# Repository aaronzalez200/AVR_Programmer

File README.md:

# AVR_Programmer

Small board with mounting holes that was designed to easily place an Arduino that runs software that programs an external board that contains an AVR chip via ICSP. Display included to show the user the testing process and if any errors have occurred.

Designed using KiCad

Early prototype using Arduino MEGA later updated for UNO:

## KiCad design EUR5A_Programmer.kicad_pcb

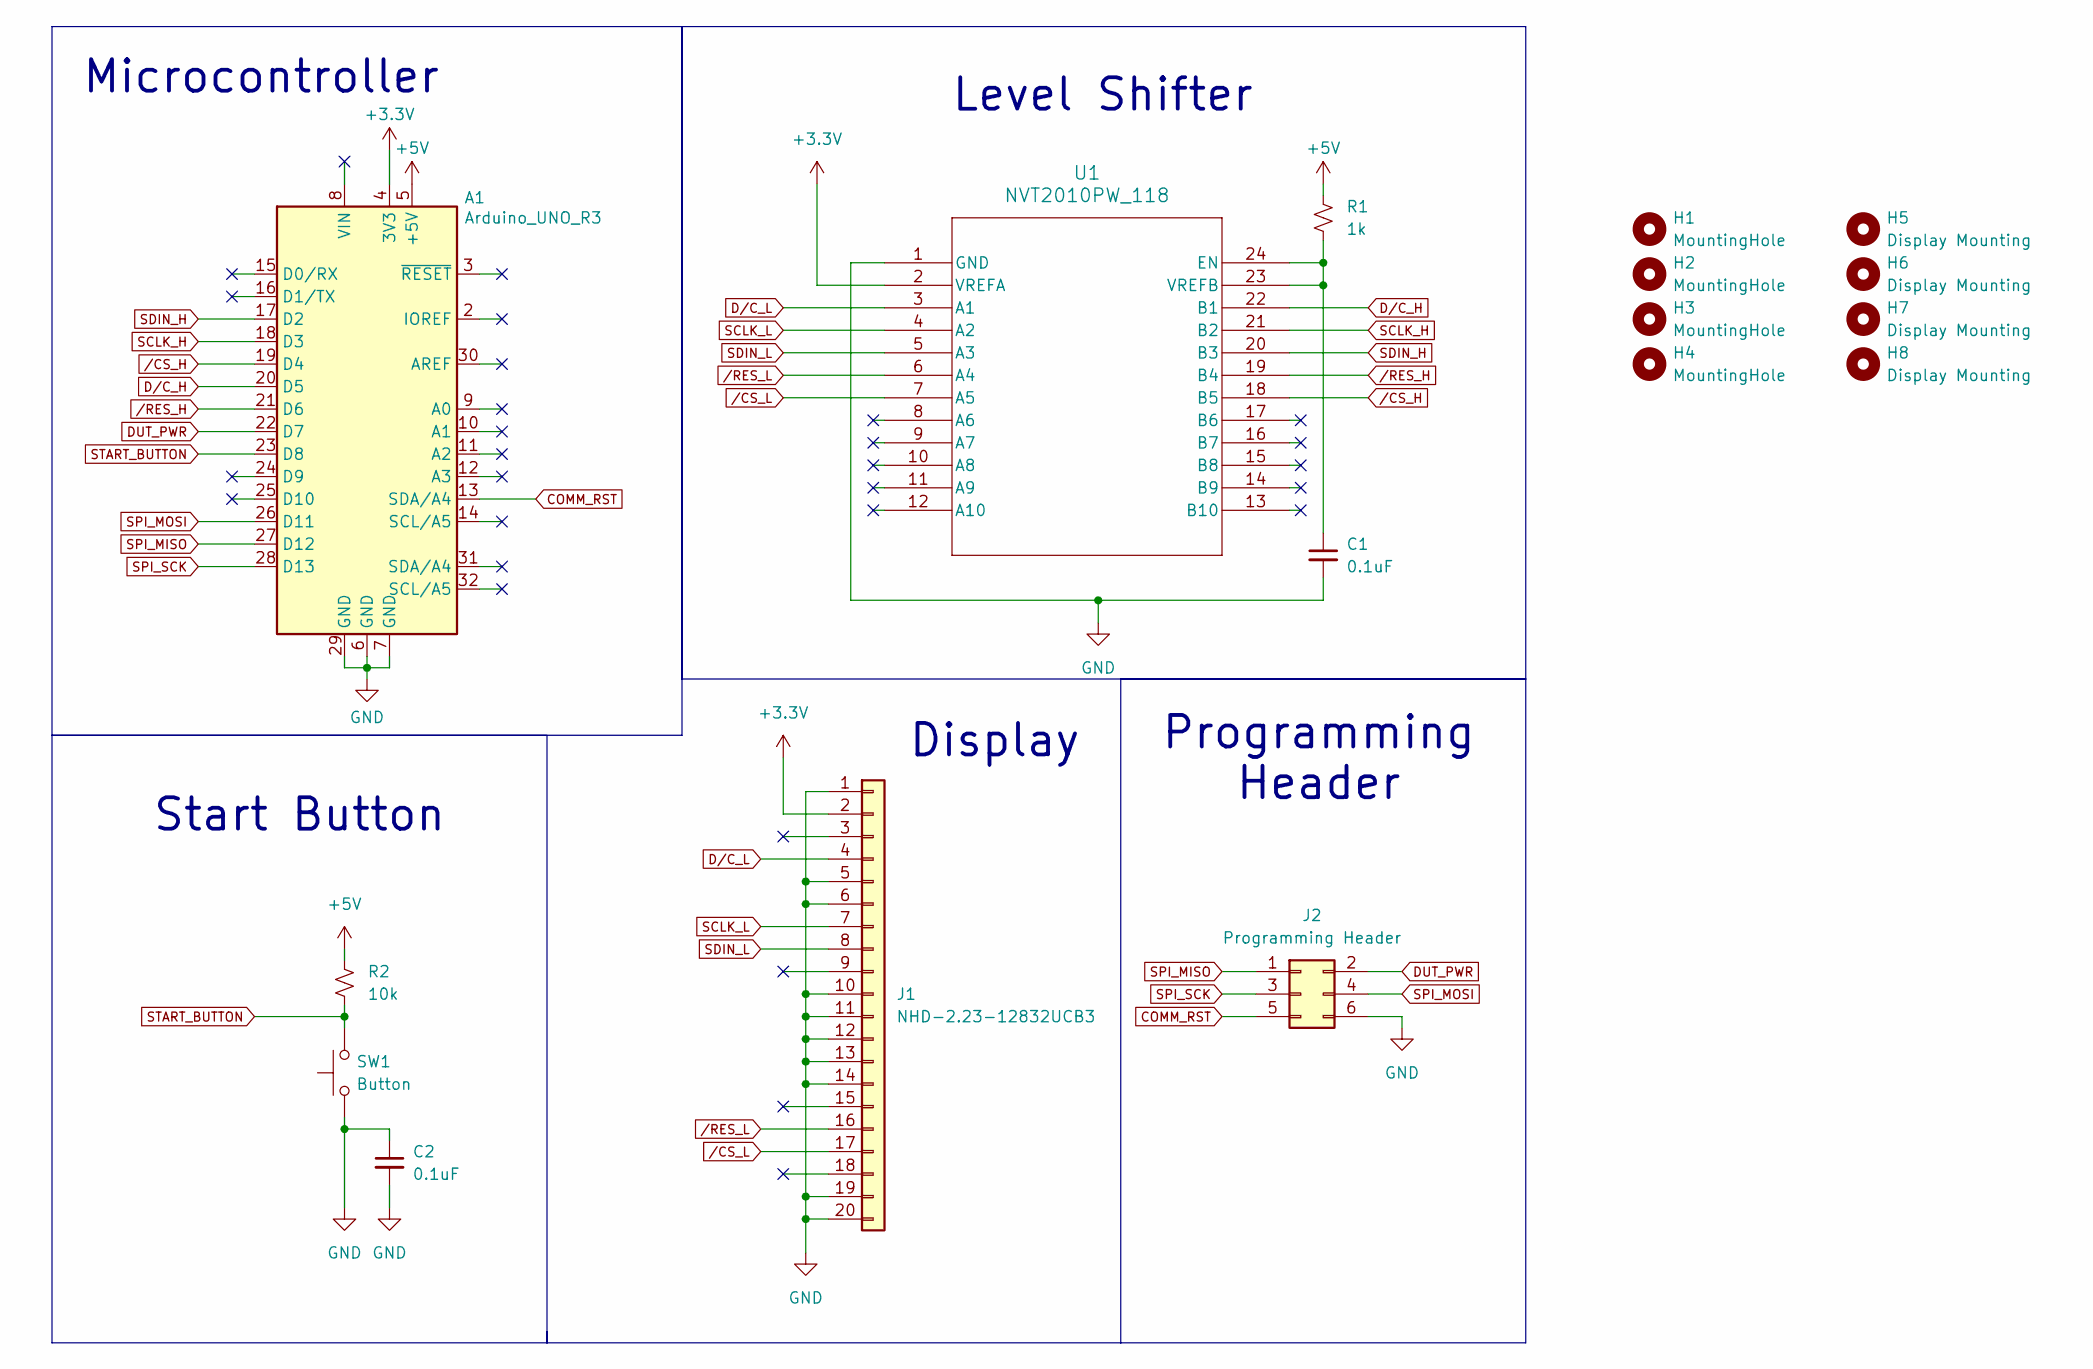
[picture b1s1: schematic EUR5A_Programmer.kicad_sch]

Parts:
A1: Arduino_UNO_R3
C1, C2: 0.1uF; C_Axial_L3.8mm_D2.6mm_P7.50mm_Horizontal
H1, H2, H3, H4: MountingHole; MountingHole_3mm
H5, H6, H7, H8: Display Mounting; Display_Mounting_Hole
J1: NHD-2.23-12832UCB3; PinHeader_1x20_P2.54mm_Vertical
J2: Programming Header; IDC-Header_2x03_P2.54mm_Vertical
R1: 1k; R_Axial_DIN0411_L9.9mm_D3.6mm_P12.70mm_Horizontal
R2: 10k; R_Axial_DIN0411_L9.9mm_D3.6mm_P12.70mm_Horizontal
SW1: Button; TerminalBlock_bornier-2_P5.08mm
U1: NVT2010PW_118; TSSOP24_SOT355-1_NXP

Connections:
+3.3V: A1.4 (3V3), J1.2, U1.2 (VREFA)
+5V: A1.5 (+5V), R1.1, R2.1
COMM_RST: A1.13 (SDA/A4), J2.5
DUT_PWR: A1.22 (D7), J2.2
D/C_H: A1.20 (D5), U1.22 (B1)
D/C_L: J1.4, U1.3 (A1)
GND: A1.6 (GND), A1.7 (GND), A1.29 (GND), C1.2, C2.1, C2.2, J1.1, J1.5, J1.6, J1.10, J1.11, J1.12, J1.13, J1.14, J1.19, J1.20, J2.6, SW1.1, U1.1 (GND)
unnamed: C1.1, R1.2, U1.23 (VREFB), U1.24 (EN)
SCLK_H: A1.18 (D3), U1.21 (B2)
SCLK_L: J1.7, U1.4 (A2)
SDIN_H: A1.17 (D2), U1.20 (B3)
SDIN_L: J1.8, U1.5 (A3)
SPI_MISO: A1.27 (D12), J2.1
SPI_MOSI: A1.26 (D11), J2.4
SPI_SCK: A1.28 (D13), J2.3
START_BUTTON: A1.23 (D8), R2.2, SW1.2
/CS_H: A1.19 (D4), U1.18 (B5)
/CS_L: J1.17, U1.7 (A5)
/RES_H: A1.21 (D6), U1.19 (B4)
/RES_L: J1.16, U1.6 (A4)

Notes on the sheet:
Start Button
Microcontroller
Programming Header
Display
Level Shifter

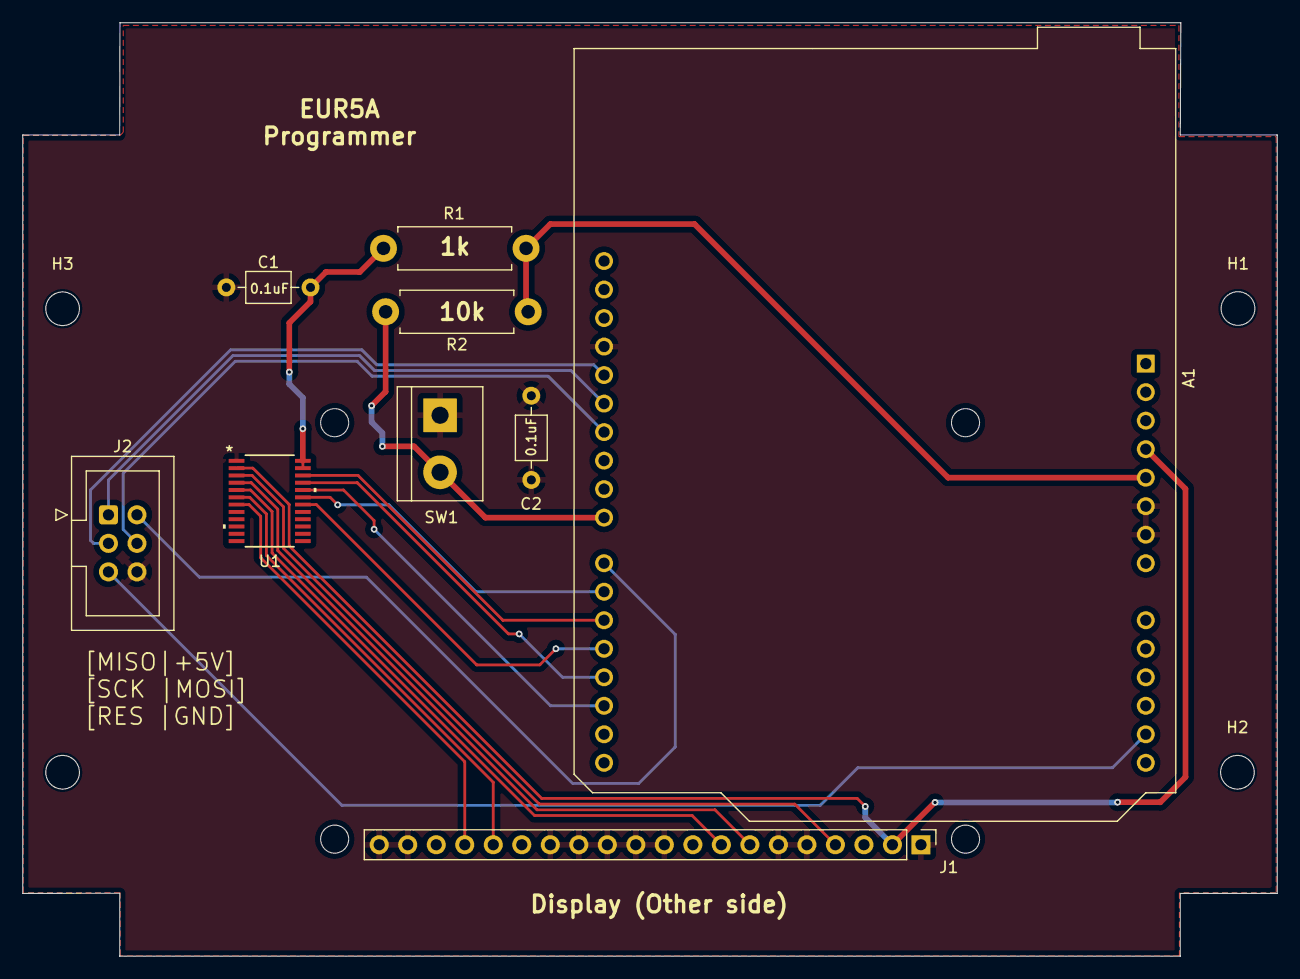
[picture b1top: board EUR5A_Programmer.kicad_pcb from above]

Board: 2 copper layers, 111.8 x 83.2 mm, 17 parts (0 on the bottom side), 20 nets.

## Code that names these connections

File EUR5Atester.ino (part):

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#include <avr/pgmspace.h>
#include "program.h"

#define START_BUTTON    8
#define COMM_RST        A4

#if defined(__AVR_ATmega2560__)
    #define SPI_SCK         52
    #define SPI_MISO        50
    #define SPI_MOSI        51
    #define SPI_CS          53
    // display stuff here
    #define SDIN            46
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    #define DC              47
    #define RES             44
    // DUT power
    #define DUT_PWR         31
#else // using UNO 
    #define SPI_SCK         13
    #define SPI_MISO        12
    #define SPI_MOSI        11
    #define SPI_CS          10
    // display stuff here
    #define SDIN            2
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    #define DC              5
    #define RES             6
    // DUT power
    #define DUT_PWR         7
#endif


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char doTest(void);

void initIOs() {
  pinMode(DUT_PWR, OUTPUT);
  digitalWrite(DUT_PWR, LOW);

  pinMode(CS, OUTPUT);
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  pinMode(SDIN, OUTPUT);
  pinMode(RES, OUTPUT);

  pinMode(COMM_RST, OUTPUT);

  // Set bits 0 1 of PORTB, bit 5 of PORTC, bit 2 of PORTD, as inputs
  pinMode(START_BUTTON, INPUT);

  // Set falling edge trigger for INT0
  EICRA |= (1 << ISC01);
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void initSPImaster(void) {
  // Set CS, MOSI, and SCK output, all others input */
  pinMode(SPI_CS, OUTPUT);
  pinMode(SPI_MOSI, OUTPUT);
  pinMode(SPI_SCK, OUTPUT);
  pinMode(SPI_MISO, INPUT);
  // Enable SPI, Master, set clock rate fck/16 */
  SPCR = (1<<SPE)|(1<<MSTR)| (1<<SPR1)|(1<<SPR0);
}
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
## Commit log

2025-03-14 added images
2025-03-14 Code & PCB
